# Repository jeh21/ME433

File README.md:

###Joe Harris
# MECH_ENG 433: Advanced Mechatronics</br>
</br>
This repository holds all of the work that I have done thus far in Advanced Mechatronics.

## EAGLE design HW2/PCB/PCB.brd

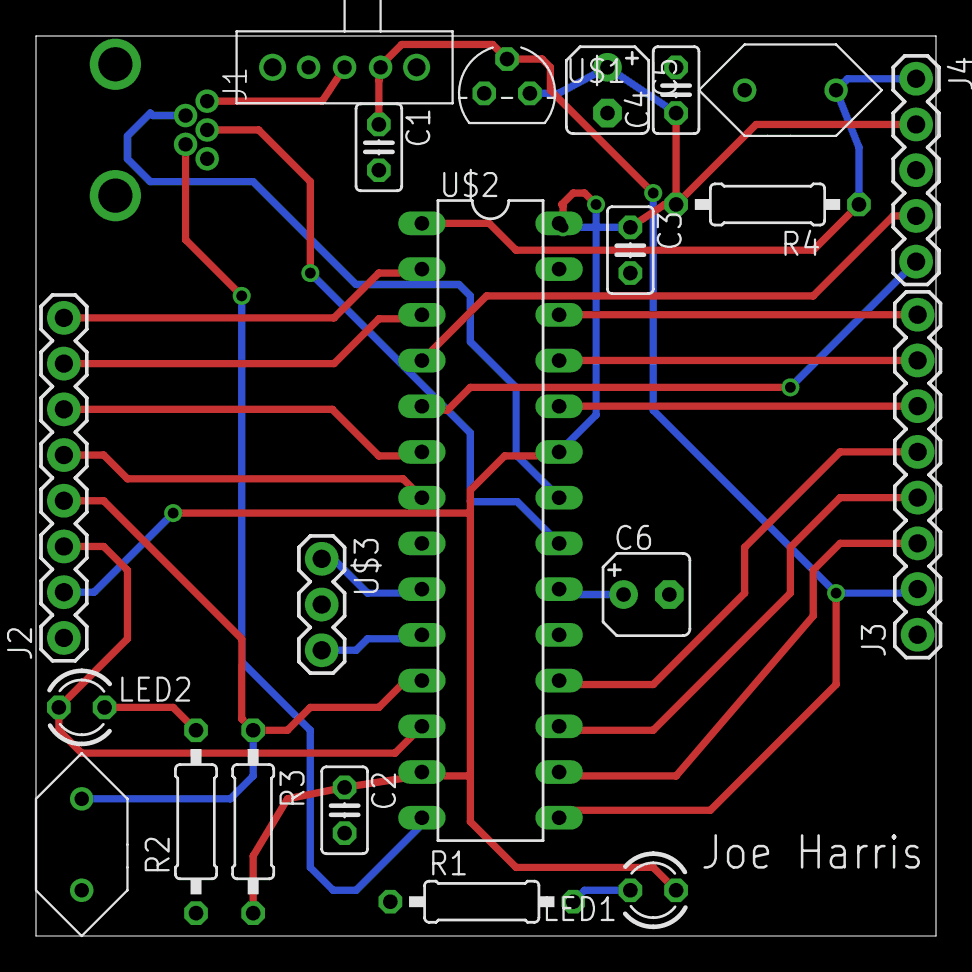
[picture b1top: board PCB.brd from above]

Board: 2 copper layers, 50.0 x 50.0 mm, 22 parts (0 on the bottom side), 27 nets.

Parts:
C1, C3, C4: 0.1uF; C025-025X050
C2: C025-025X050
C5, C6: 10uF; B45181A
J1: USB-MB-H
J2, J3: 1X08_ROUND
J4: 1X05
LED1: red; LED3MM
LED2: green; LED3MM
R1, R2: 330; 0207/10
R3, R4: 0207/10
RESET: PB; PUSHBUTTON
U$1: MCP1702; TO92
U$2: PIC32MX250F128B; DIL28-3
U$3: 1X03
U$4: SLIDE
USER: PB; PUSHBUTTON

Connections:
+3V3: C2.1, C3.1, C4.1, C5.+, J2.2, J4.2, LED1.A, R3.2, R4.2, U$1.3, U$2.13, U$2.23, U$2.28
+5V: C1.1, J3.2, U$1.2, U$2.15, U$4.P$2
A0: J2.8, U$2.2
A1: J2.7, U$2.3
A4/LED: J2.3, LED2.A, U$2.12
B2: J2.6, U$2.6
B3: J2.5, U$2.7
B4/USER: J2.4, R3.1, U$2.11, USER.P$1
B7: J3.3, U$2.16
B8: J3.4, U$2.17
B9: J3.5, U$2.18
B13: J3.6, U$2.24
B14: J3.7, U$2.25
B15: J3.8, U$2.26
D+: J1.D+, U$2.21
D-: J1.D-, U$2.22
GND: C1.2, C2.2, C3.2, C4.2, C5.-, C6.-, J1.GND, J2.1, J3.1, J4.3, R1.1, R2.1, RESET.P$2, U$1.1, U$2.8, U$2.19, U$2.27, U$3.2, USER.P$2
MCLR: J4.1, R4.1, RESET.P$1, U$2.1
unnamed: J1.VBUS, U$4.P$1
unnamed: LED2.K, R2.2
unnamed: LED1.K, R1.2
unnamed: C6.+, U$2.20
unnamed: U$2.10, U$3.3
unnamed: U$2.9, U$3.1
PGC: J4.5, U$2.5
PGD: J4.4, U$2.4
USBID: J1.ID, U$2.14

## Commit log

2016-04-05 pictures added
2016-04-05 From Windows MPLAB X IDE
2016-04-05 Adding code and updated pictures
2016-04-13 Initial HW2 Upload
2016-04-14 Final update to HW2, including HW3
2016-04-14 Updated with gerber files
2016-04-14 Ready to be checked before order
2016-04-14 Ready to be checked before order, Pt. 2
2016-04-20 Initial upload
2016-04-21 Updated with HW1 main.c to set up PIC
2016-05-09 Initialized HW5
2016-05-10 Working on debugging
2016-05-11 Printing to screen, picture added
2016-05-11 Minor updates and comments
2016-05-11 App completed
2016-05-29 Added LCD .h and .c files
2016-05-29 Minor update, moved fn definitions to ILI9163 .c and .h files
2016-05-29 Successfully writing data to LCD
2016-05-30 Retitled to reflect that it is HW 2 and 3 combined
2016-05-30 Minor updates
2016-05-30 Mouse functions properly
2016-06-05 HW8 upload
2016-06-05 Initial upload, still not working
2016-06-05 Added screenshot
2016-06-06 Working
2016-06-06 Restricts landscape orientation
2016-06-06 Updated with thresholding and 2 COM
2016-06-06 Wheel.prt with picture of printed wheel
2016-06-07 Added picture of box
2016-06-09 added picture of IMU on screen
2016-06-09 Updated with .dxf and .prt files, pictures, and screenshots
2016-06-09 Added CAD Screenshots
2016-06-09 Final App uploaded
2016-06-09 Final PIC CDC code
2016-06-09 Results and pictures uploaded
